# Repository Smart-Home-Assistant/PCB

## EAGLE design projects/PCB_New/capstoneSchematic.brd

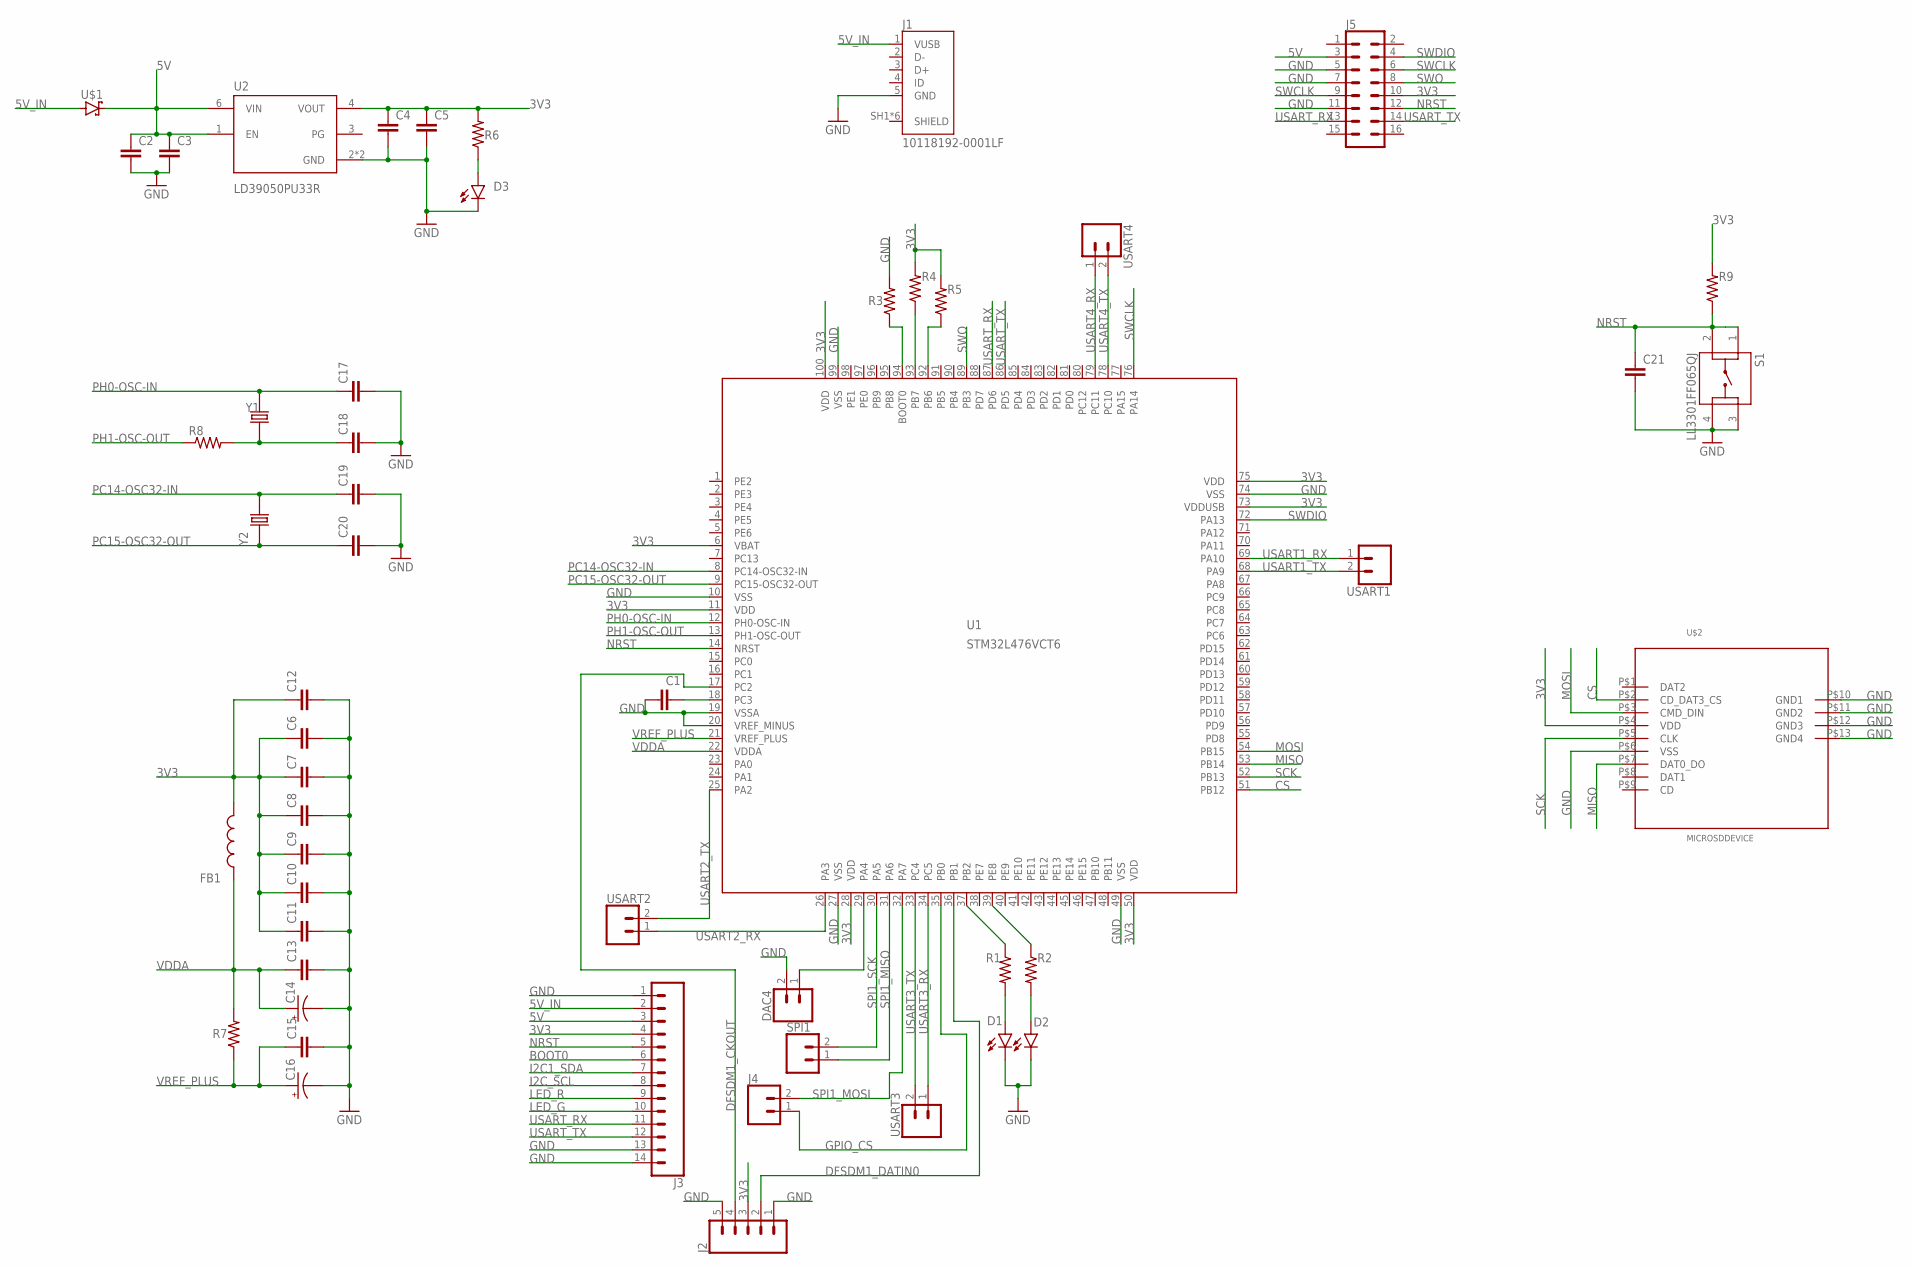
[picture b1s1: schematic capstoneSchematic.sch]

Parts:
C1, C2, C4, C12: CC0603KRX5R7BB105; CAPC1608X90
C3, C5, C6, C7, C8, C9, C10, C11, C13, C15, C21: CC0402KRX7R7BB104; CAPC1005X55N
C14, C16: TAJA105K016RNJ; CAPPM3216X180N
C17, C18: CC0402JRNPO9BN200; CAPC1005X55N
C19, C20: CC0402CRNPO9BN4R7; CAPC1005X55N
D1, D2, D3: SML-P12MTT86; LED_SML-P11UTT86R
DAC4: CONN_02; 1X02
FB1: BK1608HS601-T; BEADC1608X95N
J1: 10118192-0001LF; AMPHENOL_10118192-0001LF
J2: CONN_05LOCK; 1X05_LOCK
J3: CONN_14; 1X14
J4: CONN_02; 1X02
J5: CONN_08X2_HEADER; 2X8
R1, R2, R3, R4, R5, R6, R7: RC0402FR-071KL; RESC1005X40N
R8: RC0402FR-072KL; RESC1005X40N
R9: RC0402FR-0710KL; RESC1005X40N
S1: LL3301FF065QJ
SPI1: CONN_02; 1X02
U1: STM32L476VCT6; LQFP100_14X14
U2: LD39050PU33R; SON95P300X300X100-7N
U$1: STPS1L30A; DIOM5226X223N
U$2: MICROSDDEVICE; MICROSD
USART1, USART2, USART3, USART4: CONN_02; 1X02
Y1: ABLS-8.000MHZ-B2-T; XTAL_ABLS-8.000MHZ-B2-T
Y2: ECS-.327-12.5-12QS-TR; XTAL_ECS-.327-12.5-12QS-TR

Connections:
3V3: C4.1, C5.1, C6.1, C7.1, C8.1, C9.1, C10.1, C11.1, C12.1, FB1.2, J2.3, J3.4, J5.10, R4.2, R5.2, R6.2, R9.2, U1.6 (VBAT), U1.11 (VDD), U1.28 (VDD), U1.50 (VDD), U1.73 (VDDUSB), U1.75 (VDD), U1.100 (VDD), U2.4 (VOUT), U$2.P$4 (VDD)
5V: C2.1, C3.1, J3.3, J5.3, U2.1 (EN), U2.6 (VIN), U$1.1 (C)
5V_IN: J1.1 (VUSB), J3.2, U$1.2 (A)
BOOT0: J3.6
CS: U1.51 (PB12), U$2.P$2 (CD_DAT3_CS)
DFSDM1_CKOUT: J2.4, U1.17 (PC2)
DFSDM1_DATIN0: J2.2, U1.36 (PB1)
GND: C1.1, C2.2, C3.2, C4.2, C5.2, C6.2, C7.2, C8.2, C9.2, C10.2, C11.2, C12.2, C13.2, C14.C (-), C15.2, C16.C (-), C17.2, C18.2, C19.2, C20.2, C21.2, D1.C, D2.C, D3.C, DAC4.2, J1.5 (GND), J2.1, J2.5, J3.1, J3.13, J3.14, J5.5, J5.7, J5.11, R3.2, S1.3, S1.4, U1.10 (VSS), U1.19 (VSSA), U1.20 (VREF_MINUS), U1.27 (VSS), U1.49 (VSS), U1.74 (VSS), U1.99 (VSS), U2.2 (GND), U2.7 (GND), U$2.P$6 (VSS), U$2.P$10 (GND1), U$2.P$11 (GND2), U$2.P$12 (GND3), U$2.P$13 (GND4)
GPIO_CS: J4.1, U1.35 (PB0)
I2C1_SDA: J3.7
I2C_SCL: J3.8
LED_G: J3.10
LED_R: J3.9
MISO: U1.53 (PB14), U$2.P$7 (DAT0_DO)
MOSI: U1.54 (PB15), U$2.P$3 (CMD_DIN)
unnamed: R2.1, U1.39 (PE8)
unnamed: R1.1, U1.37 (PB2)
unnamed: D1.A, R1.2
unnamed: D2.A, R2.2
unnamed: R3.1, U1.94 (BOOT0)
unnamed: R4.1, U1.93 (PB7)
unnamed: R5.1, U1.92 (PB6)
unnamed: D3.A, R6.1
unnamed: C1.2, U1.18 (PC3)
unnamed: C18.1, R8.2, Y1.1
unnamed: DAC4.1, U1.29 (PA4)
NRST: C21.1, J3.5, J5.12, R9.1, S1.2, U1.14 (NRST)
PC14-OSC32-IN: C19.1, U1.8 (PC14-OSC32-IN), Y2.2
PC15-OSC32-OUT: C20.1, U1.9 (PC15-OSC32-OUT), Y2.1
PH0-OSC-IN: C17.1, U1.12 (PH0-OSC-IN), Y1.2
PH1-OSC-OUT: R8.1, U1.13 (PH1-OSC-OUT)
SCK: U1.52 (PB13), U$2.P$5 (CLK)
SPI1_MISO: SPI1.1, U1.31 (PA6)
SPI1_MOSI: J4.2, U1.32 (PA7)
SPI1_SCK: SPI1.2, U1.30 (PA5)
SWCLK: J5.6, J5.9, U1.76 (PA14)
SWDIO: J5.4, U1.72 (PA13)
SWO: J5.8, U1.89 (PB3)
USART1_RX: U1.69 (PA10), USART1.1
USART1_TX: U1.68 (PA9), USART1.2
USART2_RX: U1.26 (PA3), USART2.1
USART2_TX: U1.25 (PA2), USART2.2
USART3_RX: U1.34 (PC5), USART3.1
USART3_TX: U1.33 (PC4), USART3.2
USART4_RX: U1.79 (PC11), USART4.1
USART4_TX: U1.78 (PC10), USART4.2
USART_RX: J3.11, J5.13, U1.87 (PD6)
USART_TX: J3.12, J5.14, U1.86 (PD5)
VDDA: C13.1, C14.A (+), FB1.1, R7.2, U1.22 (VDDA)
VREF_PLUS: C15.1, C16.A (+), R7.1, U1.21 (VREF_PLUS)

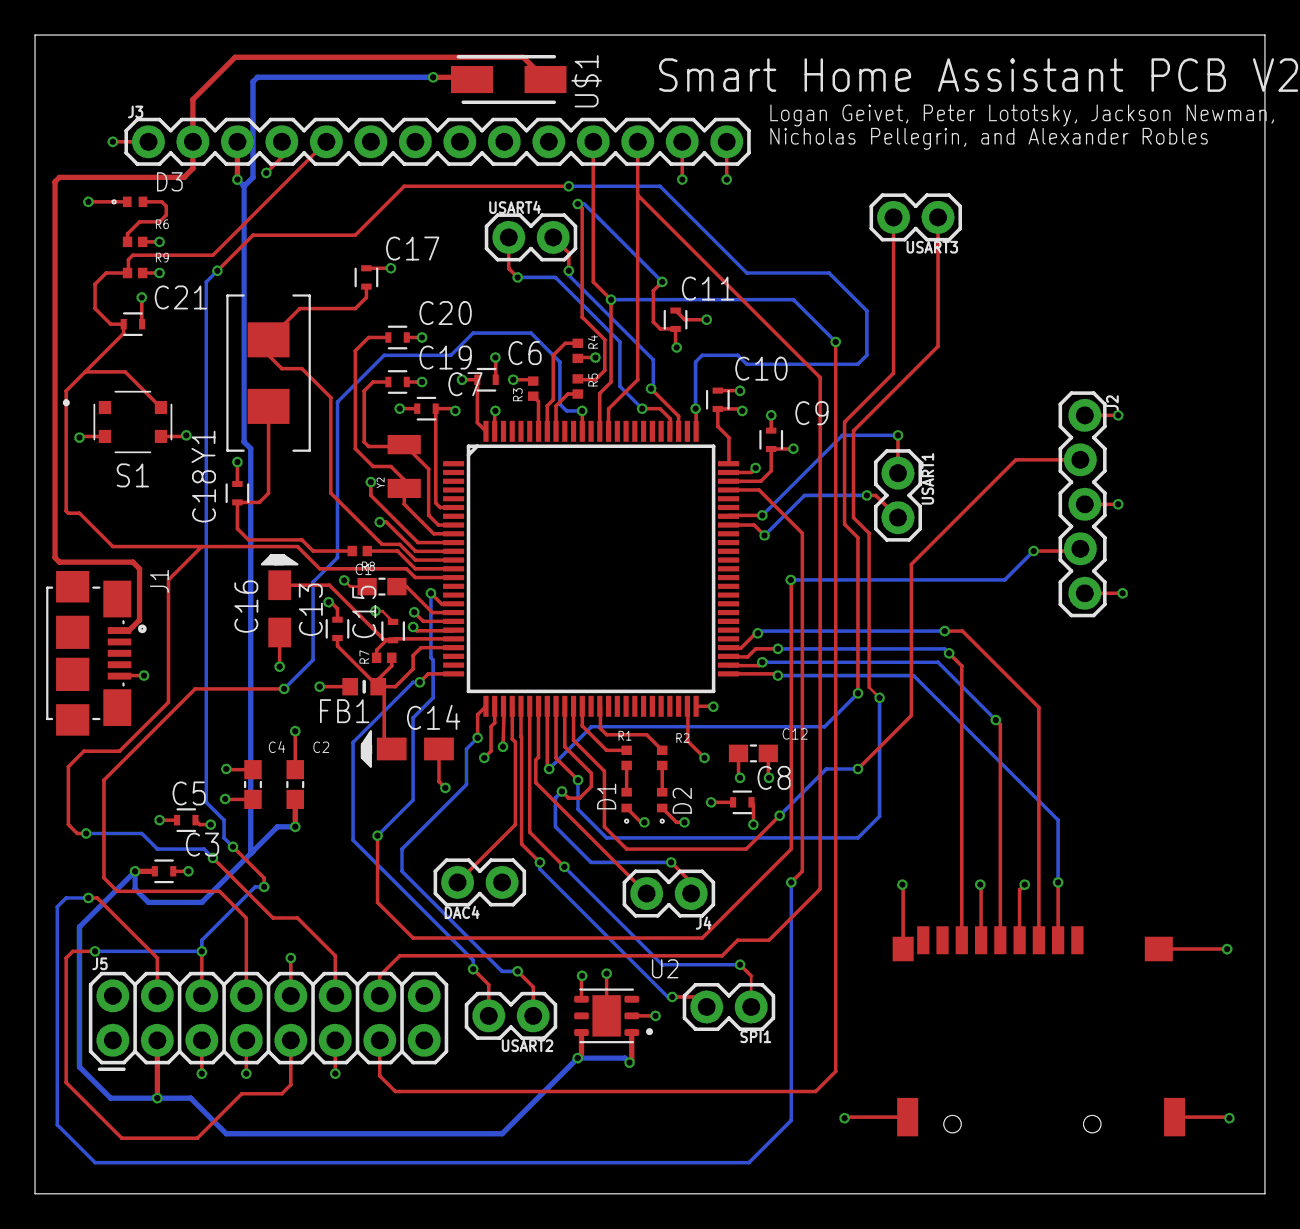
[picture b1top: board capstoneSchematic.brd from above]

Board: 4 copper layers, 70.2 x 66.2 mm, 52 parts (0 on the bottom side), 45 nets.

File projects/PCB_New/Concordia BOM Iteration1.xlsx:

Comment | Designator | Footprint | JLC Part #
1μF | C1, C2, C4, C12 | CAPC1608X90 | C106215
0.1μF | C3, C5, C6, C7, C8, C9, C10, C11, C13, C15 | CAPC1005X55N | C60474
1μF | C14, C16 | CAPPM3216X180N | C7174
20pF | C17, C18 | CAPC1005X55N | C107000
4.7pF | C9, C20 | CAPC1005X55N | C189469
0.1μF | C21 | CAPC1005X55N | C60474
395mV@1A | U$1 | DIOM5226X223N | C222239
SML-P1 | D1, D2, D3 | LED_SML-P11UTT86R | C510304
A±20ppm | Y1 | XTAL_ABLS-8.000MHZ-B2-T | C2842266
32.768kHz 12.5pF ±20ppm | Y2 | XTAL_ECS-.327-12.5-12QS-TR | C5361379
1K | R1, R2, R3, R4, R5, R6, R7 | RESC1005X40N | C106235
2K | R8 | RESC1005X40N | C60488
10K | R9 | RESC1005X40N | C60490
3.3K | R10, R14, R15, R16 | RESC1005X40 | C2935239
Micro B USB 2.0 | J1 | AMPHENOL_10118192-0001LF | C132564
P=2.54mm Female Headers ROHS | J5 | 2X8 (Version 2) | C30734 | 2x8 pin header
P=2.54mm | J3 | 1X14 (Version 2) | C2905420 | 14 pin header
MicroSD Card slot | U$2 | MICROSD | C7529389
50mA 12VDC | S1 | LL3301FF065QJ | C221902 | switch
Fixed 3.3V Positive 5.5V | U2 | SON95P300X300X100-7N | C132827
TSSOP-14 | U3 | IC_74LVC125APW,118 | C6059
600 Ohms @ 100 MHz 1 Ferrite Bead | FB1 | BEADC1608X95N | C87552
2mm 3A Plugin | USART1, USART2, USART3, USART4, SPI1, DAC4 | 1X02 (Version 2) | C7499322 | 2 pin header
54Mbps 2.4GHz WiFi I2C | U4 | ﻿ESP8266EX | C77967

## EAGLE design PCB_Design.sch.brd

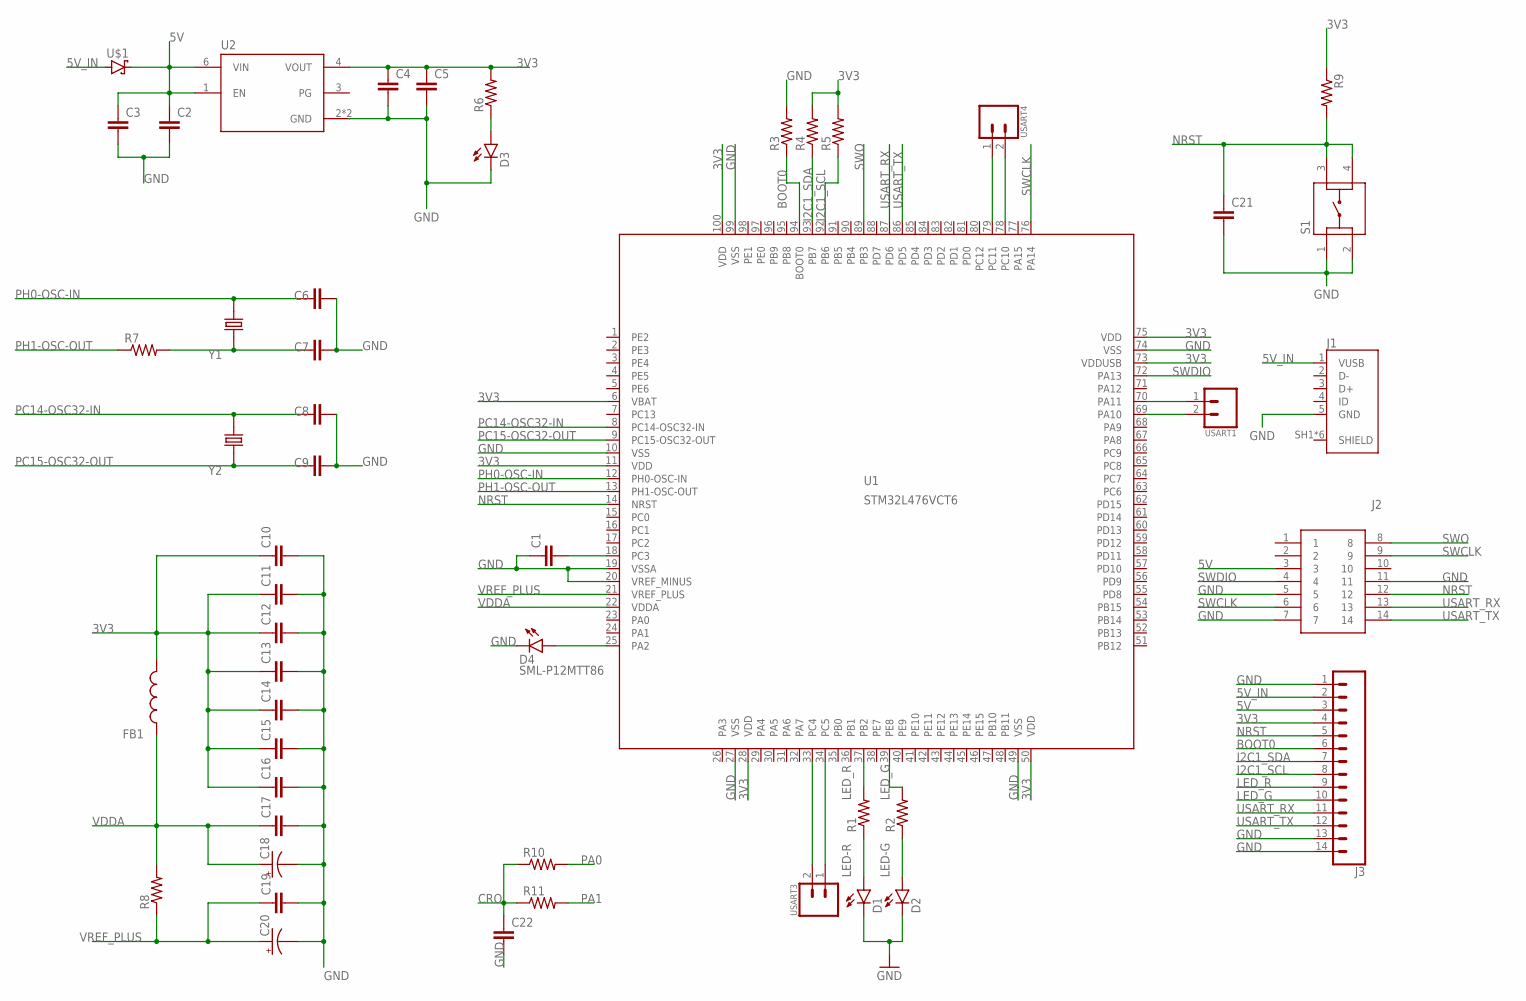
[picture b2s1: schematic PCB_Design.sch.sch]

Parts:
C1, C2, C3, C4, C5, C10: CC0603KRX5R7BB105; CAPC1608X90
C6, C7: CC0402JRNPO9BN200; CAPC1005X55N
C8, C9: CC0402CRNPO9BN4R7; CAPC1005X55N
C11, C12, C13, C14, C15, C16, C17, C19, C21, C22: CC0402KRX7R7BB104; CAPC1005X55N
C18, C20: TAJA105K016RNJ; CAPPM3216X180N
D1, D2, D4: SML-P12MTT86; LED_SML-P11UTT86R
D3: SML-P12VTT86; LED_SML-P11UTT86R
FB1: BK1608HS601-T; BEADC1608X95N
J1: 10118192-0001LF; AMPHENOL_10118192-0001LF
J2: FTSH-107-01-L-DV-K-A; FTSH10701LDVKA
J3: CONN_14; 1X14
R1, R2, R3, R4, R5, R6, R7, R8, R9: RC0402FR-071KL; RESC1005X40N
R10: RC0402FR-0710KL; RESC1005X40N
R11: RC0402FR-07330RL; RESC1005X40N
S1: LL3301FF065QJ
U1: STM32L476VCT6; LQFP100_14X14
U2: LD39050PU33R; SON95P300X300X100-7N
U$1: STPS1L30A; DIOM5226X223N
USART1, USART3, USART4: CONN_02LOCK; 1X02_LOCK
Y1: ABLS-8.000MHZ-B2-T; XTAL_ABLS-8.000MHZ-B2-T
Y2: ECS-.327-12.5-12QS-TR; XTAL_ECS-.327-12.5-12QS-TR

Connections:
3V3: C4.1, C5.1, C10.1, C11.1, C12.1, C13.1, C14.1, C15.1, C16.1, FB1.2, J3.4, R4.2, R5.2, R6.2, R9.1, U1.6 (VBAT), U1.11 (VDD), U1.28 (VDD), U1.50 (VDD), U1.73 (VDDUSB), U1.75 (VDD), U1.100 (VDD), U2.4 (VOUT)
5V: C2.1, C3.1, J2.3, J3.3, U2.1 (EN), U2.6 (VIN), U$1.1 (C)
5V_IN: J1.1 (VUSB), J3.2, U$1.2 (A)
BOOT0: J3.6, R3.1, U1.94 (BOOT0)
CRO: C22.1, R10.1, R11.1
GND: C1.1, C2.2, C3.2, C4.2, C5.2, C6.2, C7.2, C8.2, C9.2, C10.2, C11.2, C12.2, C13.2, C14.2, C15.2, C16.2, C17.2, C18.C (-), C19.2, C20.C (-), C21.2, C22.2, D1.C, D2.C, D3.C, D4.C, J1.5 (GND), J2.5, J2.7, J2.11, J3.1, J3.13, J3.14, R3.2, S1.1, S1.2, U1.10 (VSS), U1.19 (VSSA), U1.20 (VREF_MINUS), U1.27 (VSS), U1.49 (VSS), U1.74 (VSS), U1.99 (VSS), U2.2 (GND), U2.7 (GND)
I2C1_SCL: J3.8, R5.1, U1.92 (PB6)
I2C1_SDA: J3.7, R4.1, U1.93 (PB7)
LED-G: D2.A, R2.1
LED-R: D1.A, R1.1
LED_G: J3.10, R2.2, U1.39 (PE8)
LED_R: J3.9, R1.2, U1.37 (PB2)
unnamed: D4.A, U1.25 (PA2)
unnamed: U1.33 (PC4), USART3.2
unnamed: U1.34 (PC5), USART3.1
unnamed: U1.78 (PC10), USART4.2
unnamed: U1.69 (PA10), USART1.2
unnamed: U1.79 (PC11), USART4.1
unnamed: U1.70 (PA11), USART1.1
unnamed: C7.1, R7.2, Y1.1
unnamed: C1.2, U1.18 (PC3)
unnamed: D3.A, R6.1
NRST: C21.1, J2.12, J3.5, R9.2, S1.3, S1.4, U1.14 (NRST)
PA0: R10.2
PA1: R11.2
PC14-OSC32-IN: C8.1, U1.8 (PC14-OSC32-IN), Y2.2
PC15-OSC32-OUT: C9.1, U1.9 (PC15-OSC32-OUT), Y2.1
PH0-OSC-IN: C6.1, U1.12 (PH0-OSC-IN), Y1.2
PH1-OSC-OUT: R7.1, U1.13 (PH1-OSC-OUT)
SWCLK: J2.6, J2.9, U1.76 (PA14)
SWDIO: J2.4, U1.72 (PA13)
SWO: J2.8, U1.89 (PB3)
USART_RX: J2.13, J3.11, U1.87 (PD6)
USART_TX: J2.14, J3.12, U1.86 (PD5)
VDDA: C17.1, C18.A (+), FB1.1, R8.2, U1.22 (VDDA)
VREF_PLUS: C19.1, C20.A (+), R8.1, U1.21 (VREF_PLUS)

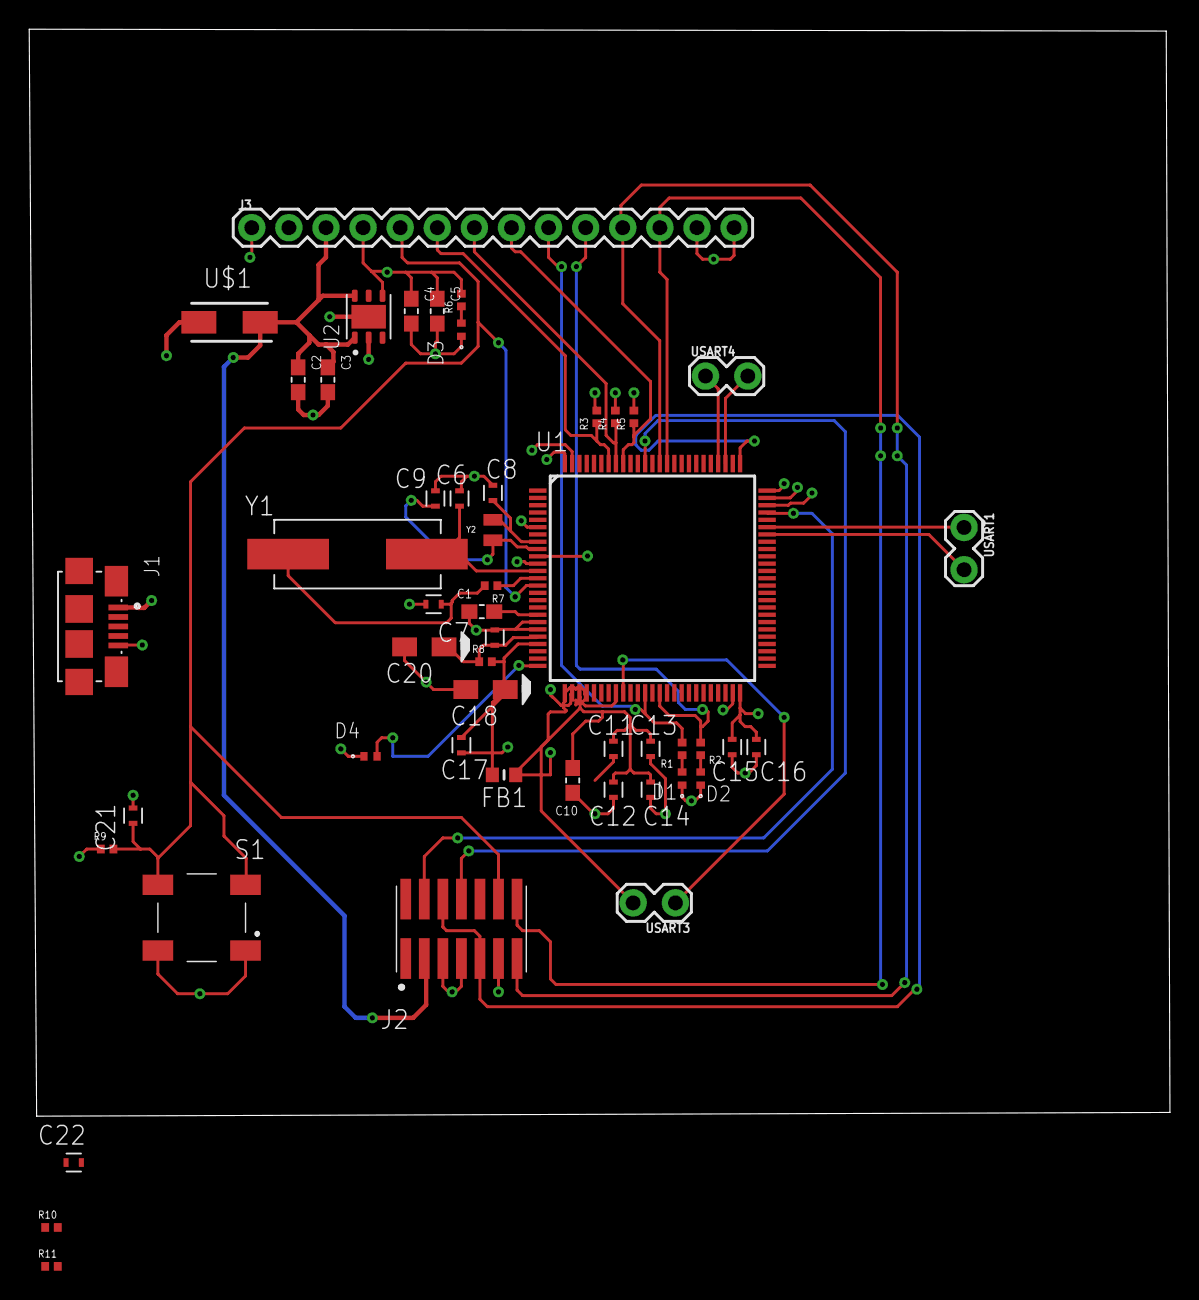
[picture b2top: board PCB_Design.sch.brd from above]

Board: 4 copper layers, 78.1 x 74.4 mm, 50 parts (0 on the bottom side), 34 nets.

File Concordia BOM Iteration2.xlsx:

Comment | Designator | Footprint | JLC Part #
1μF | C1, C2, C4, C12 | CAPC1608X90 | C106215
0.1μF | C3, C5, C6, C7, C8, C9, C10, C11, C13, C15 | CAPC1005X55N | C60474
1μF | C14, C16 | CAPPM3216X180N | C7174
20pF | C17, C18 | CAPC1005X55N | C107000
4.7pF | C9, C20 | CAPC1005X55N | C189469
0.1μF | C21 | CAPC1005X55N | C60474
395mV@1A | U$1 | DIOM5226X223N | C222239
SML-P1 | D1, D2, D3 | LED_SML-P11UTT86R | C510304
A±20ppm | Y1 | XTAL_ABLS-8.000MHZ-B2-T | C2842266
32.768kHz 12.5pF ±20ppm | Y2 | XTAL_ECS-.327-12.5-12QS-TR | C5361379
1K | R1, R2, R3, R4, R5, R6, R7 | RESC1005X40N | C106235
2K | R8 | RESC1005X40N | C60488
10K | R9 | RESC1005X40N | C60490
3.3K | R10, R14, R15, R16 | RESC1005X40 | C2935239
Micro B USB 2.0 | J1 | AMPHENOL_10118192-0001LF | C132564
P=2.54mm Female Headers ROHS | J5 | 2X8 (Version 2) | C30734 | 2x8 pin header
P=2.54mm | J3 | 1X14 (Version 2) | C2905420 | 14 pin header
MicroSD Card slot | U$2 | MICROSD | C7529389
50mA 12VDC | S1 | LL3301FF065QJ | C221902 | switch
Fixed 3.3V Positive 5.5V | U2 | SON95P300X300X100-7N | C132827
TSSOP-14 | U3 | IC_74LVC125APW,118 | C6059
600 Ohms @ 100 MHz 1 Ferrite Bead | FB1 | BEADC1608X95N | C87552
2mm 3A Plugin | USART1, USART2, USART3, USART4, SPI1, DAC4 | 1X02 (Version 2) | C7499322 | 2 pin header
54Mbps 2.4GHz WiFi I2C | U4 | ﻿ESP8266EX | C77967

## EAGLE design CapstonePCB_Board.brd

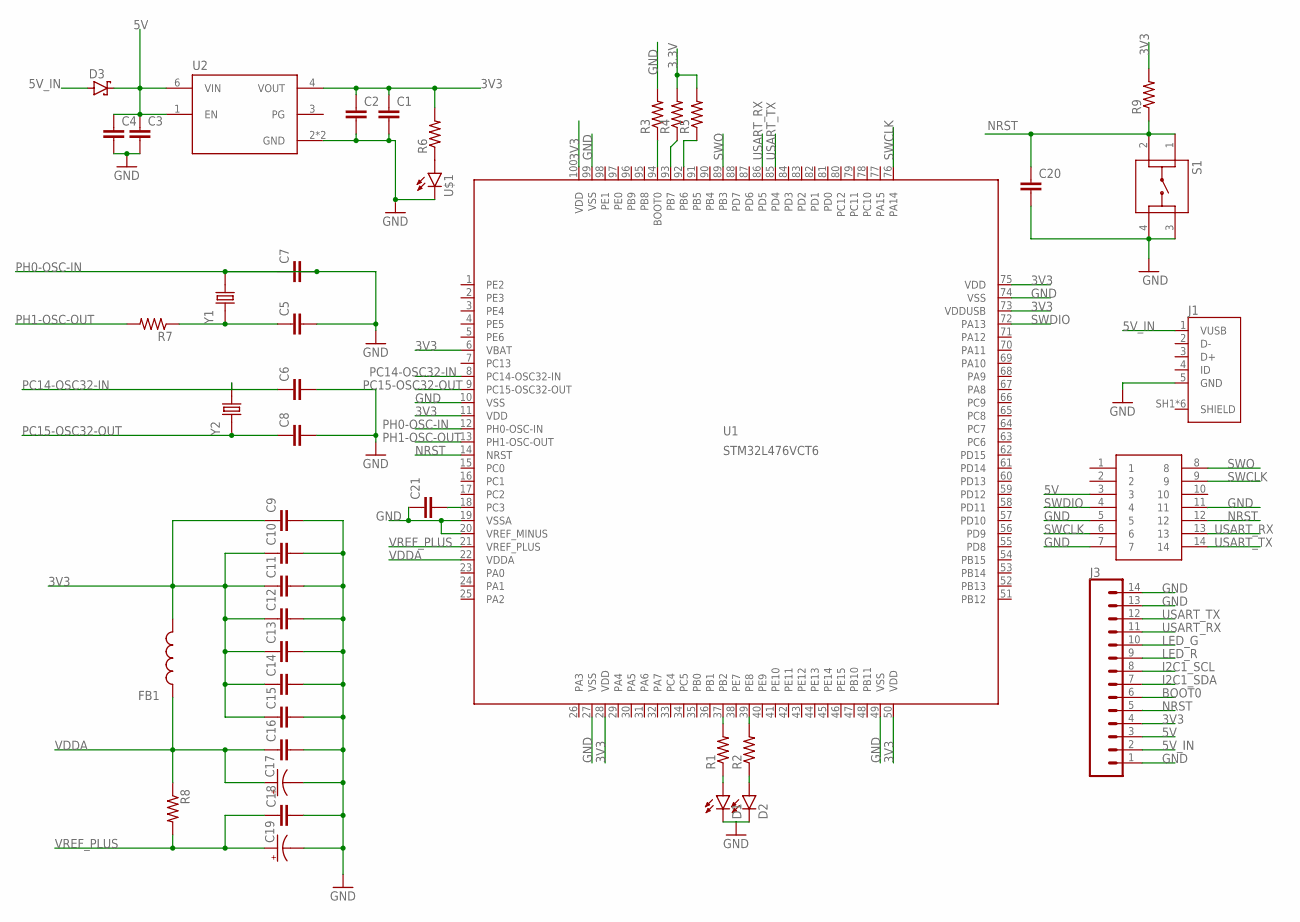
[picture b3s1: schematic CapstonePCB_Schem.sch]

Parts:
C1, C2, C3, C4, C5, C6, C7, C8, C21: CC0402JRNPO9BN200; CAPC1005X55N
C9, C10, C11, C12, C13, C14, C15, C16, C18: CC0603KRX5R7BB105; CAPC1608X90
C17, C19: TAJA105K016RNJ; CAPPM3216X180N
C20: CC0402KRX7R7BB104; CAPC1005X55N
D1, D2: SML-P12MTT86; LED_SML-P11UTT86R
D3: BAT54; SOT23
FB1: BK1608HS601-T; BEADC1608X95N
J1: 10118192-0001LF; AMPHENOL_10118192-0001LF
J2: FTSH-107-01-L-DV-K-A; FTSH10701LDVKA
J3: CONN_14; 1X14
R1, R2, R3, R4, R5, R6, R7, R8, R9: RC0402FR-071KL; RESC1005X40N
S1: LL3301FF065QJ
U1: STM32L476VCT6; LQFP100_14X14
U2: LD39050PU33R; SON95P300X300X100-7N
U$1: 19-213-R6C-AP1Q2B/3T; CAPC0603X39N
Y1, Y2: ECS-.327-12.5-12QS-TR; XTAL_ECS-.327-12.5-12QS-TR

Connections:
3.3V: R4.2, R5.2
3V3: C1.1, C2.1, C9.1, C10.1, C11.1, C12.1, C13.1, C14.1, C15.1, FB1.2, J3.4, R6.2, R9.2, U1.6 (VBAT), U1.11 (VDD), U1.28 (VDD), U1.50 (VDD), U1.73 (VDDUSB), U1.75 (VDD), U1.100 (VDD), U2.4 (VOUT)
5V: C3.1, C4.1, D3.3 (C), J2.3, J3.3, U2.1 (EN), U2.6 (VIN)
5V_IN: D3.1 (A), J1.1 (VUSB), J3.2
BOOT0: J3.6
GND: C1.2, C2.2, C3.2, C4.2, C6.2, C8.2, C9.2, C10.2, C11.2, C12.2, C13.2, C14.2, C15.2, C16.2, C17.C (-), C18.2, C19.C (-), C20.2, C21.1, D1.C, D2.C, J1.5 (GND), J2.5, J2.7, J2.11, J3.1, J3.13, J3.14, R3.2, S1.3, S1.4, U1.10 (VSS), U1.19 (VSSA), U1.20 (VREF_MINUS), U1.27 (VSS), U1.49 (VSS), U1.74 (VSS), U1.99 (VSS), U2.2 (GND), U2.7 (GND), U$1.2 (C)
I2C1_SCL: J3.8
I2C1_SDA: J3.7
LED_G: J3.10
LED_R: J3.9
unnamed: R2.2, U1.39 (PE8)
unnamed: R1.2, U1.37 (PB2)
unnamed: D1.A, R1.1
unnamed: D2.A, R2.1
unnamed: R5.1, U1.92 (PB6)
unnamed: R6.1, U$1.1 (A)
unnamed: R3.1, U1.94 (BOOT0)
unnamed: R4.1, U1.93 (PB7)
unnamed: C5.1, R7.1, Y1.1
unnamed: C21.2, U1.18 (PC3)
NRST: C20.1, J2.12, J3.5, R9.1, S1.1, S1.2, U1.14 (NRST)
PC14-OSC32-IN: C6.1, U1.8 (PC14-OSC32-IN), Y2.2
PC15-OSC32-OUT: C8.1, U1.9 (PC15-OSC32-OUT), Y2.1
PH0-OSC-IN: C5.2, C7.1, C7.2, U1.12 (PH0-OSC-IN), Y1.2
PH1-OSC-OUT: R7.2, U1.13 (PH1-OSC-OUT)
SWCLK: J2.6, J2.9, U1.76 (PA14)
SWDIO: J2.4, U1.72 (PA13)
SWO: J2.8, U1.89 (PB3)
USART_RX: J2.13, J3.11, U1.86 (PD5)
USART_TX: J2.14, J3.12, U1.85 (PD4)
VDDA: C16.1, C17.A (+), FB1.1, R8.1, U1.22 (VDDA)
VREF_PLUS: C18.1, C19.A (+), R8.2, U1.21 (VREF_PLUS)

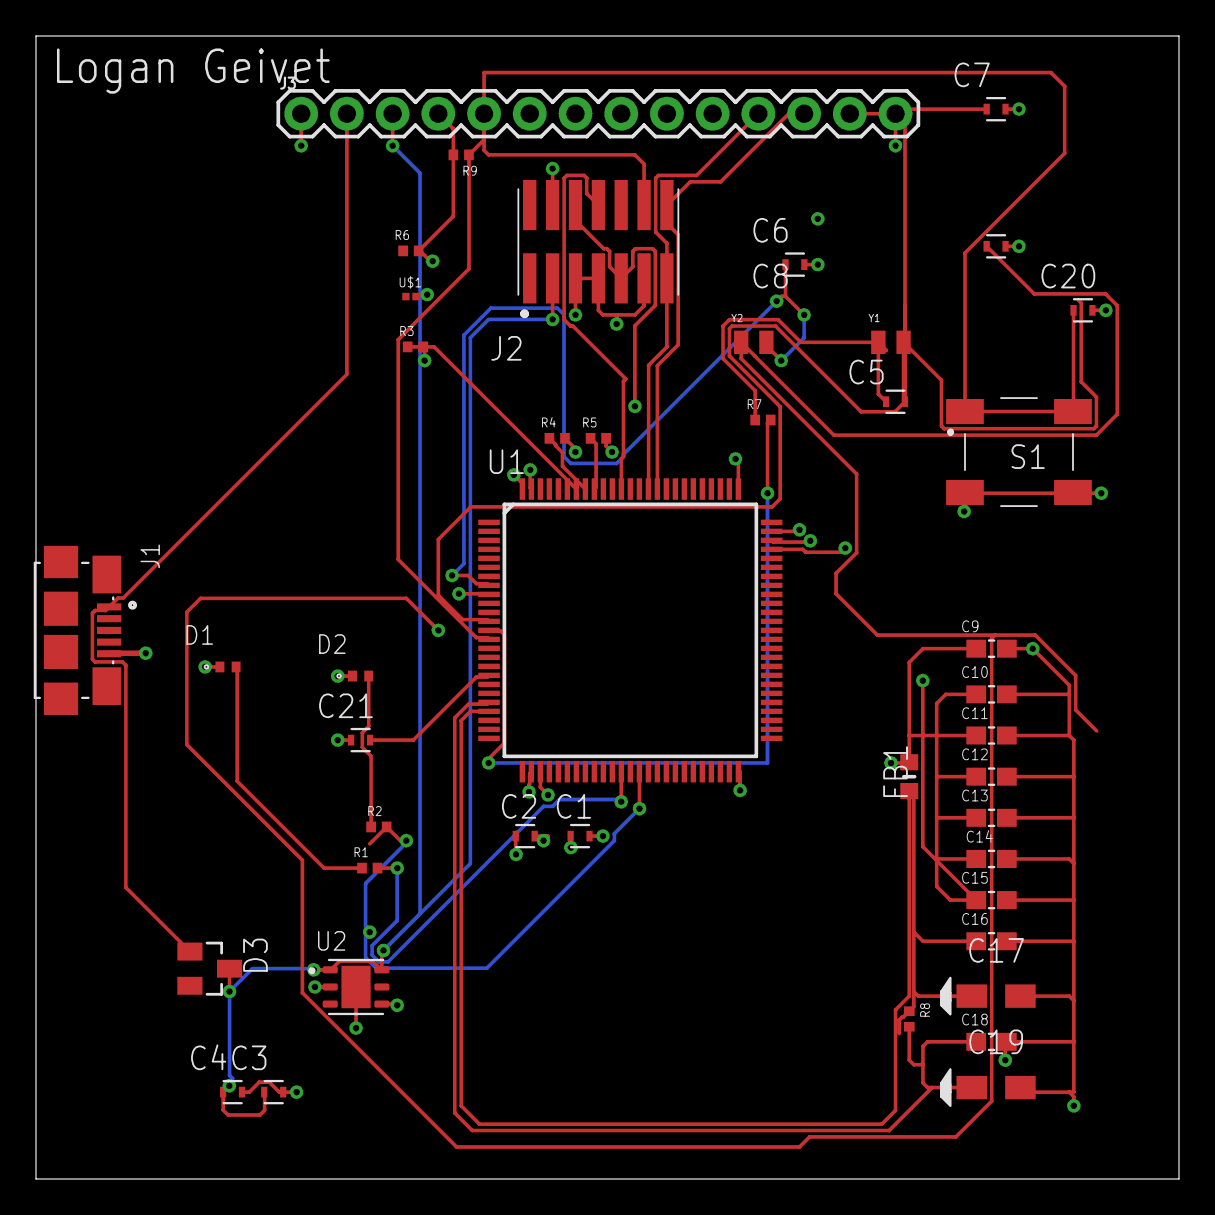
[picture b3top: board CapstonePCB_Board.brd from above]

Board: 4 copper layers, 63.5 x 63.5 mm, 43 parts (0 on the bottom side), 27 nets.

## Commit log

2024-01-24 Add files via upload
    initial commit
2024-01-29 Add files via upload
    this is the new main PCB to work with
2024-01-31 Add files via upload
    for safe keeping
2024-02-06 Add files via upload
    Finished wiring the MicroSD card slot on the board
2024-02-06 Delete PCB_2:5:24.zip
    removed since it was older
2024-02-08 Add files via upload
    New PCB with custom footprint for MicroSD card slot
2024-02-09 Add files via upload
    Fixed wiring with custom footprint
2024-02-14 Add files via upload
    PCB to be sent out for iteration 1
2024-02-28 test
2024-02-28 fixes
2024-03-06 file movement
2024-04-15 V2 Changes
2024-04-15 SD Changes
2024-04-15 SD Buffer Changes
2024-04-15 V2 Folder
2024-04-15 Final Fix
2024-04-25 Iteration 2 commit

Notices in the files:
parts and their libraries:
SparkFun-Connectors: Licensing: Creative Commons ShareAlike 4.0 International - https://creativecommons.org/licenses/by-sa/4.0
